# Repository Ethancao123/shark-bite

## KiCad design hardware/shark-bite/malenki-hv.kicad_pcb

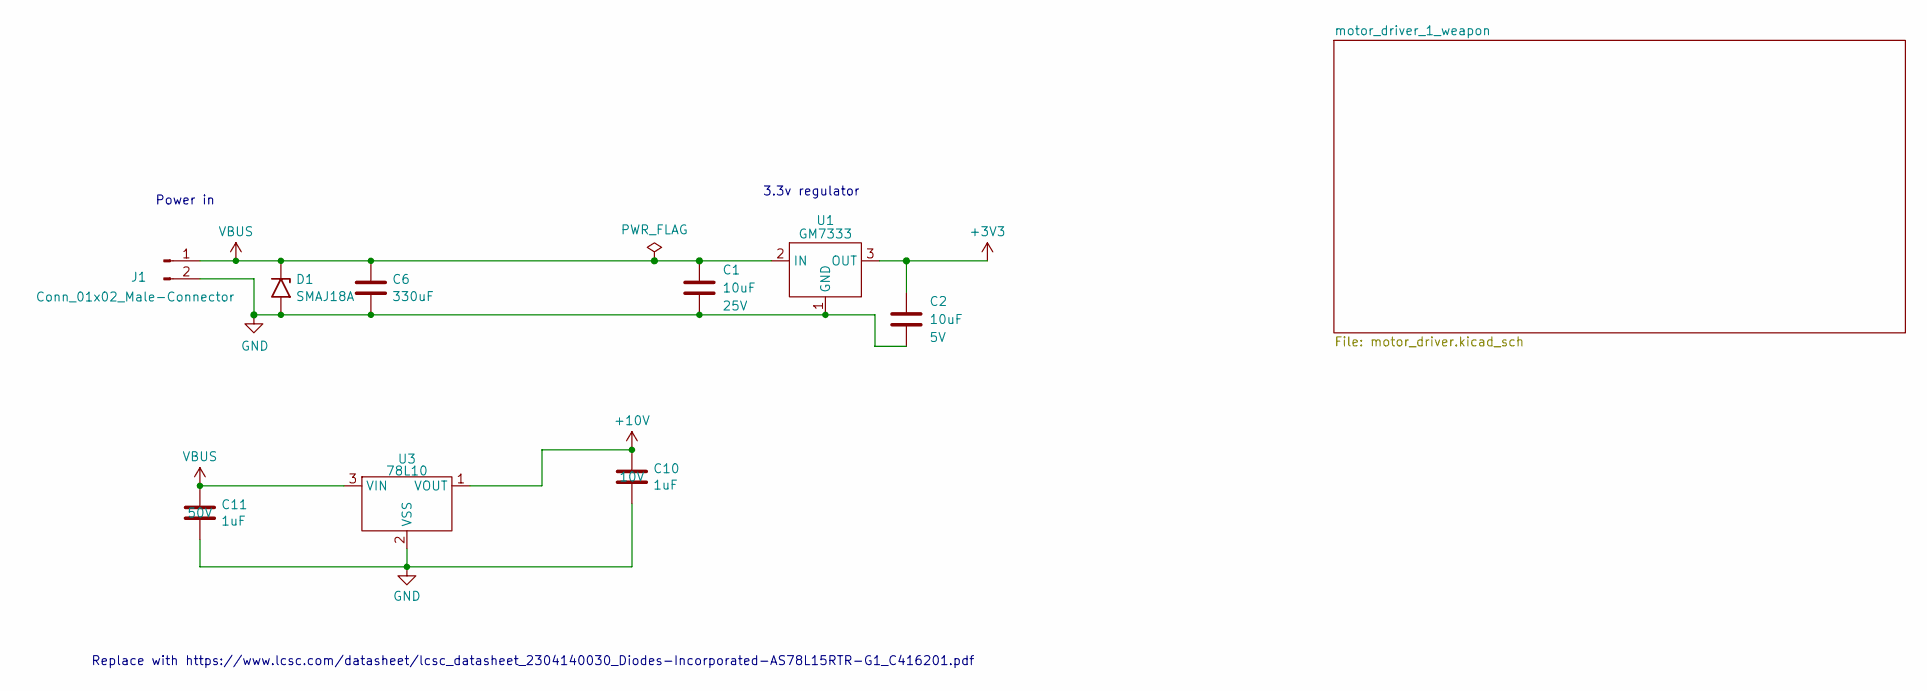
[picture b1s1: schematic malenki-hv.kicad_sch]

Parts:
C1, C2: 10uF; C_0603_1608Metric
C6: 330uF; C_0603_1608Metric
C10, C11: 1uF; C_0603_1608Metric
D1: SMAJ18A; D_SMA; LCSC C20883287
J1: Conn_01x02_Male-Connector; Power Input
U1: GM7333; SOT-89-3; LCSC C2833582
U3: 78L10; SOT-89-3; LCSC C6718417

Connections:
+3V3: C2.1, U1.3 (OUT); also elsewhere on the board
+10V: C10.1, U3.1 (VOUT); also elsewhere on the board
GND: C1.2, C2.2, C6.2, C10.2, C11.2, D1.2 (A2), J1.2, U1.1 (GND), U3.2 (VSS); also elsewhere on the board
VBUS: C1.1, C6.1, C11.1, D1.1 (A1), J1.1, U1.2 (IN), U3.3 (VIN); also elsewhere on the board

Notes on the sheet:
Power in
3.3v regulator
Replace with https://www.lcsc.com/datasheet/lcsc_datasheet_2304140030_Diodes-Incorporated-AS78L15RTR-G1_C416201.pdf

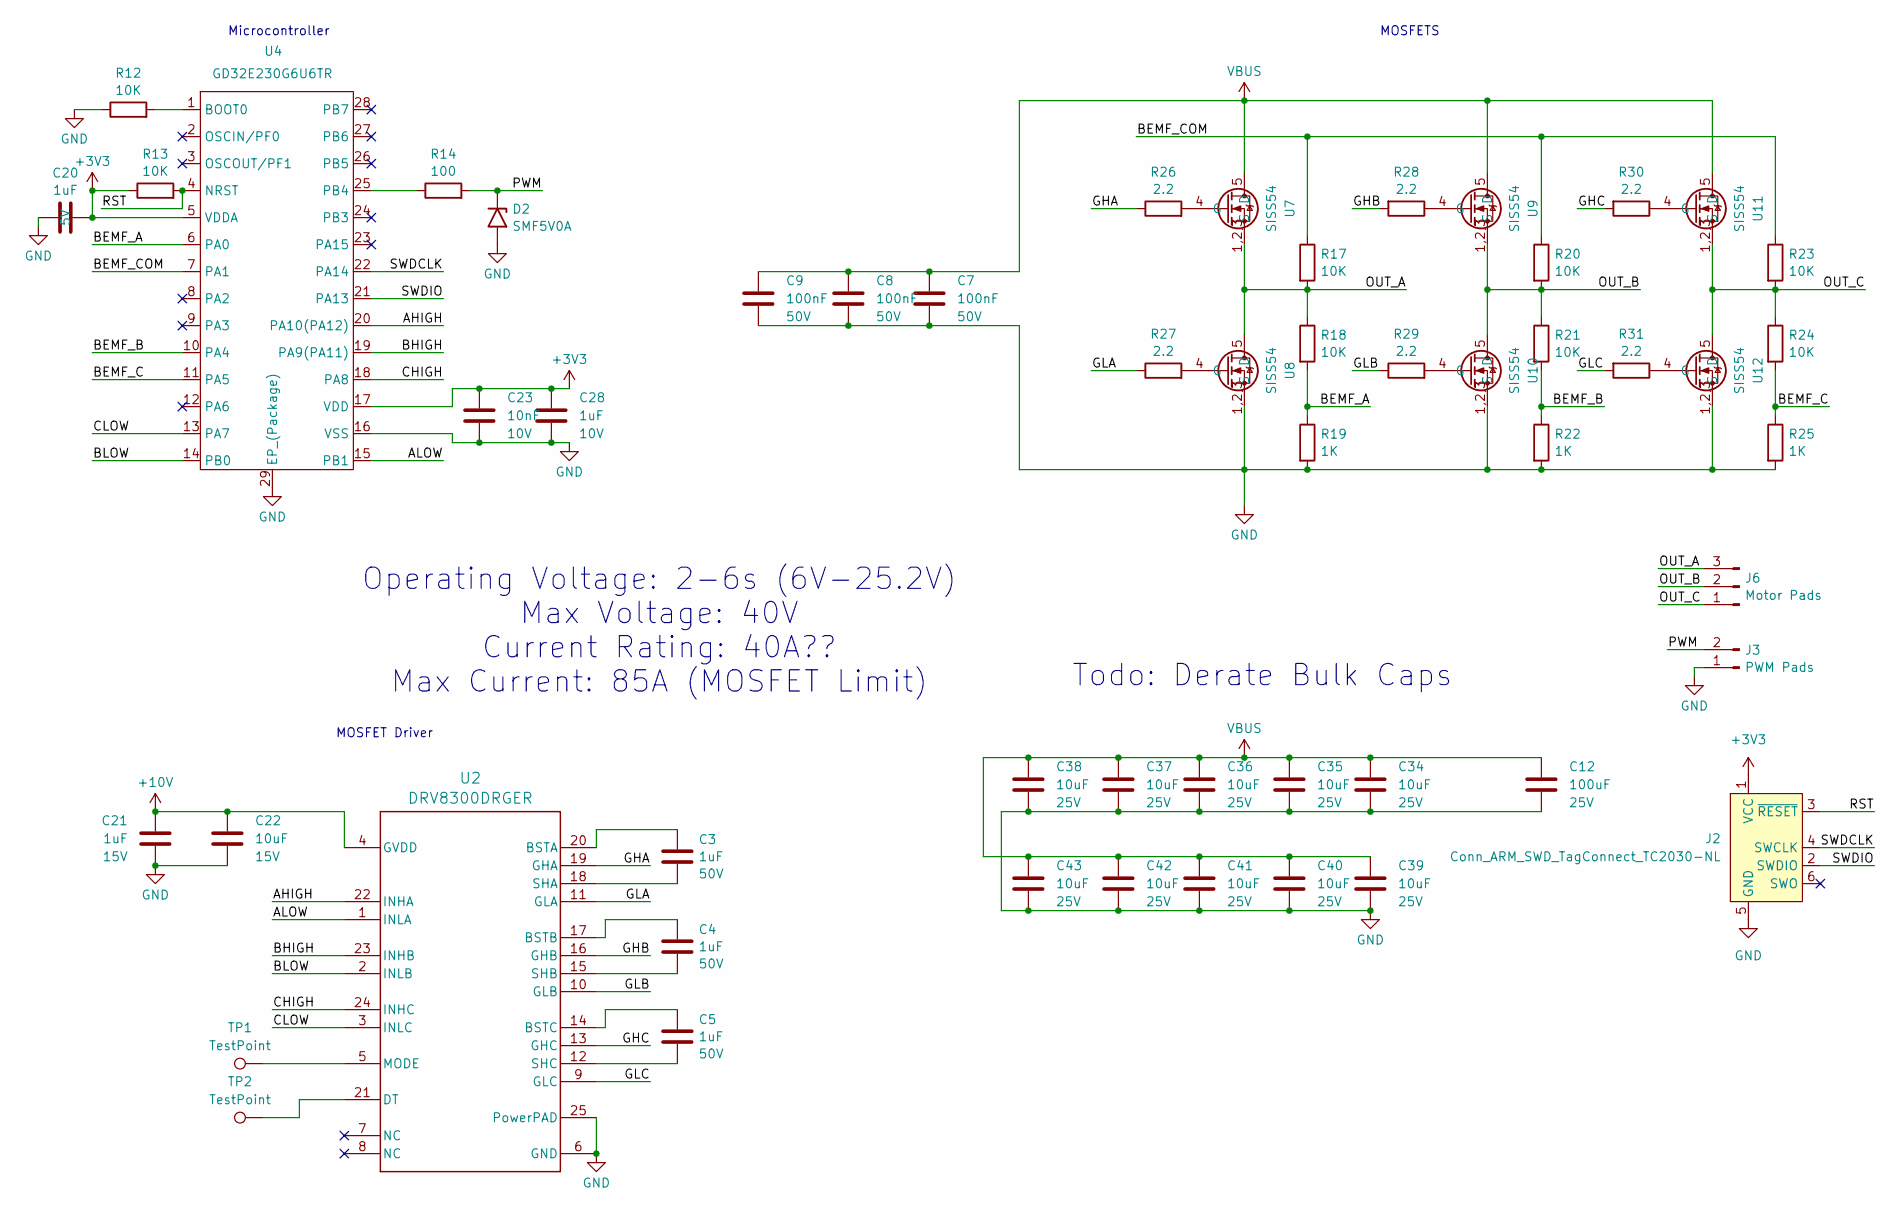
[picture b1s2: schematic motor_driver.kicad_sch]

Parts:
C3, C4, C5: 1uF; C_0603_1608Metric; LCSC C307331
C7, C8, C9: 100nF; C_0402_1005Metric; LCSC C307331
C12: 100uF; LCSC C556232
C20, C21, C28: 1uF; C_0402_1005Metric_Pad0.74x0.62mm_HandSolder
C22: 10uF; C_0402_1005Metric_Pad0.74x0.62mm_HandSolder
C23: 10nF; C_0402_1005Metric_Pad0.74x0.62mm_HandSolder
C34, C35, C36, C37, C38, C39, C40, C41, C42, C43: 10uF; C_0603_1608Metric
D2: SMF5V0A; D_SMF; LCSC C1972946
J2: Conn_ARM_SWD_TagConnect_TC2030-NL; Tag-Connect_TC2030-IDC-NL_2x03_P1.27mm_Vertical
J3: PWM Pads; PinHeader_1x02_P1.00mm_Vertical
J6: Motor Pads; ESC Pads
R12, R13, R17, R18, R20, R21, R23, R24: 10K; R_0402_1005Metric; LCSC C25744
R14: 100; R_0402_1005Metric
R19, R22, R25: 1K; R_0402_1005Metric; LCSC C11702
R26, R27, R28, R29, R30, R31: 2.2; R_0603_1608Metric
TP1, TP2: TestPoint; TestPoint_Pad_1.0x1.0mm
U2: DRV8300DRGER; RGE0024B-IPC_A
U4: GD32E230G6U6TR; QFN-28-1EP_4x4mm_P0.4mm_EP2.6x2.6mm; LCSC C2835081
U7, U8, U9, U10, U11, U12: SISS54; 1212-8S; LCSC C67862

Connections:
+3V3: C20.1, C23.2, C28.2, J2.1 (VCC), R13.1, U4.5 (VDDA), U4.17 (VDD); also elsewhere on the board
+10V: C21.2, C22.2, U2.4 (GVDD); also elsewhere on the board
/motor_driver_1_weapon/AHIGH: U2.22 (INHA), U4.20 (PA10(PA12))
/motor_driver_1_weapon/ALOW: U2.1 (INLA), U4.15 (PB1)
/motor_driver_1_weapon/BEMF_A: R18.2, R19.1, U4.6 (PA0)
/motor_driver_1_weapon/BEMF_B: R21.2, R22.1, U4.10 (PA4)
/motor_driver_1_weapon/BEMF_C: R24.2, R25.1, U4.11 (PA5)
/motor_driver_1_weapon/BEMF_COM: R17.1, R20.1, R23.1, U4.7 (PA1)
/motor_driver_1_weapon/BHIGH: U2.23 (INHB), U4.19 (PA9(PA11))
/motor_driver_1_weapon/BLOW: U2.2 (INLB), U4.14 (PB0)
/motor_driver_1_weapon/CHIGH: U2.24 (INHC), U4.18 (PA8)
/motor_driver_1_weapon/CLOW: U2.3 (INLC), U4.13 (PA7)
/motor_driver_1_weapon/GHA: R26.1, U2.19 (GHA)
/motor_driver_1_weapon/GHB: R28.2, U2.16 (GHB)
/motor_driver_1_weapon/GHC: R30.2, U2.13 (GHC)
/motor_driver_1_weapon/GLA: R27.1, U2.11 (GLA)
/motor_driver_1_weapon/GLB: R29.1, U2.10 (GLB)
/motor_driver_1_weapon/GLC: R31.2, U2.9 (GLC)
/motor_driver_1_weapon/OUT_A: J6.3, R17.2, R18.1, U7.1,2,3 (S), U8.5 (D)
/motor_driver_1_weapon/OUT_B: J6.2, R20.2, R21.1, U9.1,2,3 (S), U10.5 (D)
/motor_driver_1_weapon/OUT_C: J6.1, R23.2, R24.1, U11.1,2,3 (S), U12.5 (D)
/motor_driver_1_weapon/PWM: D2.1 (A1), J3.2, R14.2
/motor_driver_1_weapon/RST: J2.3 (~RESET), R13.2, U4.4 (NRST)
/motor_driver_1_weapon/SWDCLK: J2.4 (SWCLK), U4.22 (PA14)
/motor_driver_1_weapon/SWDIO: J2.2 (SWDIO), U4.21 (PA13)
GND: C7.2, C8.2, C9.2, C12.2, C20.2, C21.1, C22.1, C23.1, C28.1, C34.2, C35.2, C36.2, C37.2, C38.2, C39.2, C40.2, C41.2, C42.2, C43.2, D2.2 (A2), J2.5 (GND), J3.1, R12.1, R19.2, R22.2, R25.2, U2.6 (GND), U2.25 (PowerPAD), U4.16 (VSS), U4.29 (EP_(Package)), U8.1,2,3 (S), U10.1,2,3 (S), U12.1,2,3 (S); also elsewhere on the board
unnamed: C3.1, U2.20 (BSTA)
unnamed: C4.1, U2.17 (BSTB)
unnamed: C5.1, U2.14 (BSTC)
unnamed: TP2.1, U2.21 (DT)
unnamed: TP1.1, U2.5 (MODE)
unnamed: C3.2, U2.18 (SHA)
unnamed: C4.2, U2.15 (SHB)
unnamed: C5.2, U2.12 (SHC)
unnamed: R12.2, U4.1 (BOOT0)
unnamed: R14.1, U4.25 (PB4)
unnamed: R26.2, U7.4 (G)
unnamed: R27.2, U8.4 (G)
unnamed: R28.1, U9.4 (G)
unnamed: R29.2, U10.4 (G)
unnamed: R30.1, U11.4 (G)
unnamed: R31.1, U12.4 (G)
VBUS: C7.1, C8.1, C9.1, C12.1, C34.1, C35.1, C36.1, C37.1, C38.1, C39.1, C40.1, C41.1, C42.1, C43.1, U7.5 (D), U9.5 (D), U11.5 (D); also elsewhere on the board

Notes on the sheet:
Todo: Derate Bulk Caps
Operating Voltage: 2-6s (6V-25.2V) Max Voltage: 40V Current Rating: 40A?? Max Current: 85A (MOSFET Limit)
MOSFET Driver
MOSFETS
Microcontroller

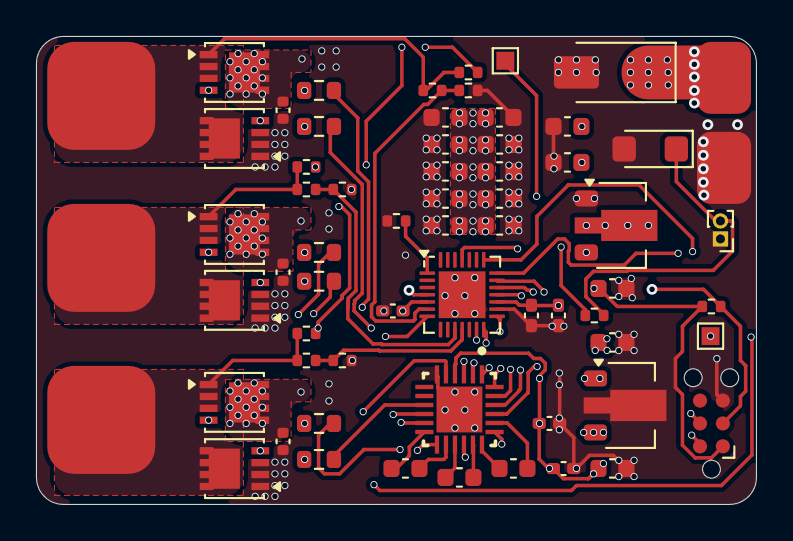
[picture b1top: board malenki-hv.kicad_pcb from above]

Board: 4 copper layers, 40.0 x 26.0 mm, 62 parts (0 on the bottom side), 43 nets.

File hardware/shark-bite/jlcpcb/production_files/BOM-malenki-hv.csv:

Comment,Designator,Footprint,LCSC
1K,"R19,R22,R25",R_0402_1005Metric,C11702
10nF,C23,C_0402_1005Metric_Pad0.74x0.62mm_HandSolder,C15195
10uF,C22,C_0402_1005Metric_Pad0.74x0.62mm_HandSolder,C15525
1uF,"C10,C11,C3,C4,C5,C7,C8,C9",C_0603_1608Metric,C15849
10uF,C2,C_0603_1608Metric,C19702
SMF5V0A,D2,D_SMF,C1972946
SMAJ18A,D1,D_SMA,C20883287
2.2,"R26,R27,R28,R29,R30,R31",R_0603_1608Metric,C22939
100,R14,R_0402_1005Metric,C25076
10K,"R12,R13,R17,R18,R20,R21,R23,R24",R_0402_1005Metric,C25744
GM7333,U1,SOT-89-3,C2833582
GD32E230G6U6TR,U4,QFN-28-1EP_4x4mm_P0.4mm_EP2.6x2.6mm,C2835081
DRV8300DRGER,U2,RGE0024B-IPC_A,C3655801
1uF,"C20,C21,C28",C_0402_1005Metric_Pad0.74x0.62mm_HandSolder,C52923
78L10,U3,SOT-89-3,C6718417
10uF,"C1,C34,C35,C36,C37,C38,C39,C40,C41,C42,C43",C_0603_1608Metric,C96446

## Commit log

2024-04-11 [ImgBot] Optimize images
    *Total -- 166.08kb -> 145.19kb (12.58%)
    /doc/channel_reverse.svg -- 30.96kb -> 21.20kb (31.52%)
    /doc/userdiag.svg -- 135.13kb -> 123.99kb (8.25%)
2024-04-22 Created ESC Microcontroller and MOSFET Driver
2024-04-22 Added TVS Diodes
2024-04-22 Removed Extra Diodes
2024-04-24 Routed
2024-04-27 Routed Without Debug
2024-04-27 Added Gate Resistors and Power Capacitors
2024-05-17 Added tag-connect
2024-06-13 Update PCB
2024-08-15 Minor Changes???
2024-08-17 Design Finished
2024-10-04 Update JLC Files
2024-10-05 Moved Intersecting Traces
